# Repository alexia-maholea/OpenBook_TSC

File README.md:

# OpenBook E-Reader
Maholea Elena-Alexia, 333CD

## Viziune de ansamblu a proiectului

## Schema bloc

# Bill of Materials
|**Part Name**                                               | **Check Price** | **DataSheet** |
|-------------------------------------------------------------|------------------|---------------|
|BUTTON| [Check Price](https://industry.panasonic.com/global/en/products/control/switch/light-touch/number/evqpuj02k)     |   [DataSheet](https://industry.panasonic.com/global/en/products/control/switch/light-touch/number/evqpuj02k)      
| ESP32_WROVER_EAGLE-LTSPICE_CC0402                          | [Check Price](https://componentsearchengine.com/part-view/CC0402MRX5R5BB106/YAGEO)      | [DataSheet](https://componentsearchengine.com/part-view/CC0402MRX5R5BB106/YAGEO)   |
|CPH3225A                                                    | [Check Price](https://www.snapeda.com/parts/CPH3225A/Seiko+Instruments/view-part/?ref=eda)      | [DataSheet](https://www.snapeda.com/parts/CPH3225A/Seiko+Instruments/view-part/?ref=eda)     |
|ADAFRUIT_LEDCHIP-LED0603                                    | [Check Price](https://www.snapeda.com/parts/KP-1608SURCK/Kingbright/view-part/?ref=search&t=LED%200603)      | [DataSheet]()     |
|USBLC6-2SC6Y                                                | [Check Price](https://www.google.com/url?q=https://www.snapeda.com/parts/USBLC6-2SC6Y/STMicroelectronics/view-part/?ref%3Deda&sa=D&source=editors&ust=1743979629785640&usg=AOvVaw2X7DsyD0aSaihvCPkvpMcS)      | [DataSheet](https://www.google.com/url?q=https://www.snapeda.com/parts/USBLC6-2SC6Y/STMicroelectronics/view-part/?ref%3Deda&sa=D&source=editors&ust=1743979629785640&usg=AOvVaw2X7DsyD0aSaihvCPkvpMcS)     |
|MBR0530                                                     | [Check Price](https://www.google.com/url?q=https://eu.mouser.com/ProductDetail/KYOCERA-AVX/SD0805S020S1R0?qs%3DjCA%25252BPfw4LHbpkAoSnwrdjw%253D%253D&sa=D&source=editors&ust=1743979672575299&usg=AOvVaw260GDj91204P1ItqGdSVkk)      | [DataSheet](https://www.google.com/url?q=https://eu.mouser.com/ProductDetail/KYOCERA-AVX/SD0805S020S1R0?qs%3DjCA%25252BPfw4LHbpkAoSnwrdjw%253D%253D&sa=D&source=editors&ust=1743979672575299&usg=AOvVaw260GDj91204P1ItqGdSVkk)     |
|PGB1010603MR                                                | [Check Price](https://www.snapeda.com/parts/PGB1010603MR/Littelfuse/view-part/?ref=eda)      | [DataSheet](https://www.snapeda.com/parts/PGB1010603MR/Littelfuse/view-part/?ref=eda)     |
| ESP32_WROVER_AVX---SD0805S020S1R0_AVX_...                  | [Check Price](https://eu.mouser.com/ProductDetail/KYOCERA-AVX/SD0805S020S1R0?qs=jCA%252BPfw4LHbpkAoSnwrdjw%3D%3D)      | [DataSheet](https://eu.mouser.com/ProductDetail/KYOCERA-AVX/SD0805S020S1R0?qs=jCA%252BPfw4LHbpkAoSnwrdjw%3D%3D)     |
| PGB1010603MR                                                | [Check Price](https://www.snapeda.com/parts/PGB1010603MR/Littelfuse/view-part/?ref=eda)      | [DataSheet](https://www.snapeda.com/parts/PGB1010603MR/Littelfuse/view-part/?ref=eda)     |
|BD5229G-TR                                                  | [Check Price](https://componentsearchengine.com/part-view/BD5229G-TR/ROHM%20Semiconductor)      | [DataSheet](https://componentsearchengine.com/part-view/BD5229G-TR/ROHM%20Semiconductor)     |
|XC6220A331MR-G                                              | [Check Price](https://componentsearchengine.com/part-view/XC6220A331MR-G/Torex)      | [DataSheet](https://componentsearchengine.com/part-view/XC6220A331MR-G/Torex)     |
|FH34SRJ-24S-0.5SH_99_                                       | [Check Price](https://componentsearchengine.com/part-view/XC6220A331MR-G/Torex)      | [DataSheet](https://componentsearchengine.com/part-view/XC6220A331MR-G/Torex)     |
|SAMACSYS_PARTS_USB4110-GF-A                                | [Check Price](https://componentsearchengine.com/part-view/USB4110-GF-A/GCT%20(GLOBAL%20CONNECTOR%20TECHNOLOGY)) | [DataSheet](https://componentsearchengine.com/part-view/USB4110-GF-A/GCT%20(GLOBAL%20CONNECTOR%20TECHNOLOGY)) |
|QWIIC_CONNECTORJS-1MM                                       | #N/A             | #N/A          |
|112A-TAAR-R03_ATTEND                                        | #N/A      | #N/A     |
|744043680IND_4828-WE-TPC_WRE                                | [Check Price](https://eu.mouser.com/ProductDetail/Wurth-Elektronik/744043680?qs=PGXP4M47uW6VkZq%252BkzjrHA%3D%3D)      | [DataSheet](https://eu.mouser.com/ProductDetail/Wurth-Elektronik/744043680?qs=PGXP4M47uW6VkZq%252BkzjrHA%3D%3D)     |
| PFMF.050.1                                      | [Check Price](https://www.mouser.co.uk/ProductDetail/EPCOS-TDK/B72520T0350K062?qs=dEfas%2FXlABIszF52uu7vrg%3D%3D)      | [DataSheet](https://www.mouser.co.uk/ProductDetail/EPCOS-TDK/B72520T0350K062?qs=dEfas%2FXlABIszF52uu7vrg%3D%3D)     |
|ESP32_WROVER_SPARKFUN-DISCRETESEMI_MOSFET_...             | [Check Price](https://componentsearchengine.com/part-view/DMG2305UX-7/Diodes%20Incorporated)      | [DataSheet](https://componentsearchengine.com/part-view/DMG2305UX-7/Diodes%20Incorporated)     |
|SJ                                                          | [Check Price](https://grabcad.com/library/solder-jumpers-1)      | [DataSheet](https://grabcad.com/library/solder-jumpers-1)     |
|ESP32_WROVER_EAGLE-LTSPICE_RR0402           | [Check Price](https://componentsearchengine.com/part-view/R0402%201%25%20100%20K%20(RC0402FR-07100KL)/YAGEO)         | [DataSheet](https://componentsearchengine.com/part-view/R0402%201%25%20100%20K%20(RC0402FR-07100KL)/YAGEO)       |
|W25Q512JVEIQ                                   | [Check Price](https://www.snapeda.com/parts/W25Q512JVEIQ/Winbond+Electronics/view-part/?ref=eda)         | [DataSheet](https://www.snapeda.com/parts/W25Q512JVEIQ/Winbond+Electronics/view-part/?ref=eda)       |
|ESP32-C6-WROOM-1-N8                            | [Check Price](https://www.snapeda.com/parts/ESP32-C6-WROOM-1-N8/Espressif+Systems/view-part/?ref=eda)         | [DataSheet](https://www.snapeda.com/parts/ESP32-C6-WROOM-1-N8/Espressif+Systems/view-part/?ref=eda)       |
|DS3231SN#                                      | [Check Price](https://www.snapeda.com/parts/DS3231SN%23/Analog+Devices/view-part/?ref=eda)         | [DataSheet](https://www.snapeda.com/parts/DS3231SN%23/Analog+Devices/view-part/?ref=eda)       |
|MAX17048G+T10                                  | [Check Price](https://www.snapeda.com/parts/MAX17048G+T10/Analog+Devices/view-part/?ref=eda)         | [DataSheet](https://www.snapeda.com/parts/MAX17048G+T10/Analog+Devices/view-part/?ref=eda)       |
|ESP32_WROVER_SPARKFUN-IC-POWER_MCP73831        | #N/A         | #N/A       |

## Descriere a functionalitatii componentelor hardware

OpenBook E-Reader este un dispozitiv portabil bazat pe ESP32-C3 WROOM, dotat cu un display e-ink de 1.5” (200x200 px) și alimentat de o baterie Li-Po. Proiectul optimizează consumul energetic și permite citirea cărților stocate pe card SD.

# Componente și interfețe

## Alimentare si Baterie

Sistemul poate fi alimentat fie prin portul USB-C, fie dintr-o baterie Li-Po, oferind flexibilitate in utilizare. Tensiunea de 5V furnizata de USB este folosita in paralel de doua componente:

- Un **controller de incarcare** pentru acumulatorul Li-Po
- Un **regulator LDO** care transforma cei 5V in 3.3V

Tensiunea de 3.3V alimenteaza toate componentele esentiale: microcontrolerul ESP32-C6, senzorii si afisajul. Cand sursa USB nu este conectata, bateria preia automat alimentarea intregului sistem.

## Microcontroler

La baza functionarii sta un **ESP32-C6**, responsabil cu:

- Rularea firmware-ului principal
- Conectarea la retele wireless (Wi-Fi 6 si BLE)
- Citirea datelor de la senzorii interni
- Afisarea informatiilor pe display-ul E-Paper
- Gestionarea memoriei externe: atat Flash NOR, cat si card microSD

## Senzori si RTC

Dispozitivul integreaza doi senzori conectati prin magistrala I2C:

- **BME688** – masoara temperatura, umiditatea, presiunea si compusi volatili
- **DS3231** – ceas de timp real (RTC) cu precizie ridicata

Prin I2C, datele sunt colectate rapid si trimise catre microcontroler pentru prelucrare.

## Display E-Paper

Afisajul de tip E-Paper comunica cu microcontrolerul prin interfata SPI si include urmatorii pini de control:

- `EPD_CS` (chip select)
- `EPD_DC` (data/command)
- `EPD_RST` (reset)
- `EPD_BUSY` (semnal de ocupat)

Actualizarea continutului pe ecran se face la cerere, iar consumul de energie este practic zero atunci cand imaginea este statica.

## Extensii si Stocare

Sistemul este gandit sa suporte si senzori aditionali printr-un conector compatibil **Qwiic / Stemma QT**, care extinde magistrala I2C. De asemenea, un **slot microSD** permite utilizatorului sa adauge fisiere externe (setari, loguri, eBooks etc.), iar o **memorie Flash NOR** dedicata stocheaza resurse interne precum firmware-ul, fonturile sau alte date statice.

# Mapping pini pentru EPS32-C6

| **Pin ESP32-C6** | **Nume/Funcție**        | **Componentă / Scop**                |
|------------------|-------------------------|--------------------------------------|
| 2                | 3V3                     | Alimentare ESP32                     |
| 1                | GND                     | Împământare                          |
| 15 (GPIO0)       | IO/BOOT                 | Mod boot pentru programare           |
| 3                | RESET                   | Reset ESP32                          |
| 23 (GPIO16)      | TXD0                    | UART TX – comunicație serială        |
| 24 (GPIO17)      | RXD0                    | UART RX – comunicație serială        |
| 27               | MISO                    | SPI – date de la dispozitiv          |
| 10               | MOSI                    | SPI – date către dispozitiv          |
| 7                | SCK                     | SPI – semnal de ceas                 |
| 4                | SS/SD                   | SPI CS – SD card                     |
| 11               | EPD_CS                  | SPI CS – e-paper                     |
| 12               | FLASH_CS                | SPI CS – Flash                       |
| 26               | EPD_BUSY                | Status e-paper                       |
| 5                | EPD_DC                  | Date/Comandă e-paper                 |
| 21               | EPD_RST                 | Reset e-paper                        |
| 18               | EPD_3V3_C               | Alimentare controlată e-paper        |
| 19               | SDA                     | I2C – date                           |
| 20               | SCL                     | I2C – ceas                           |
| 17               | I2C_PW                  | Alimentare pentru I2C (opțional)     |
| 16               | RTC_RST                 | Reset RTC                            |
| 8                | INT RTC                 | Interrupt RTC                        |
| 9                | 32KHZ                   | Oscilator extern RTC                 |
| 13, 14           | USB D-, USB D+          | Comunicare USB                       |
| 25               | IO/CHANGE               | Pin general sau întrerupere          |

# Procesul de realizare al proiectului

- In realizarea schematicului, am urmarit exact fisierul de pe OCW, iar
pentru PCB, am respectat dimensiunile si am incercat sa plasez componentele dinauntru
cat mai lizibil.

- Am realizat planurile de masa cu semnalul GND atatp e top, cat si pe bottom. Am
aplicat via stitching si am amplasat vias-urile langa antena.

- M-am folosit de autorouting pentru traseele de rutare. Am respectat cerintele de pe ocw, in legatura cu dimensiunea firelor de cupru, respectiv minim 0.30mm pentru traseele de putere si 0.15 pentru restul.

- TP-urile au fost amplasate dupa cum am considerat ca ar fi mai eficient pentru rutare
pentru a fi aproape de componentele la care sunt conectate

- Dupa ce am trecut in 3D, am adaugat componentele si le-am creat/editat modelele 3D cat sa fie asezate corespunzator pe placa.

- Pentru a scapa de erorile aparute, am efectuat diferite actiuni:
    - Pentru erorile de tip SMD-Hole, am dat Approve dupa cum ni s-a specificat
    - Pentru alte tipuri de erori, a fost nevoie sa modific footprint-ul componentelor sau sa mut firele de pe placa

- Am realizat si modele 3D pentru baterie si display, conform documentelor oferite. Am
incercat pe cat mai mult sa respect dimensiunile pentru a nu avea probleme la amplasare.

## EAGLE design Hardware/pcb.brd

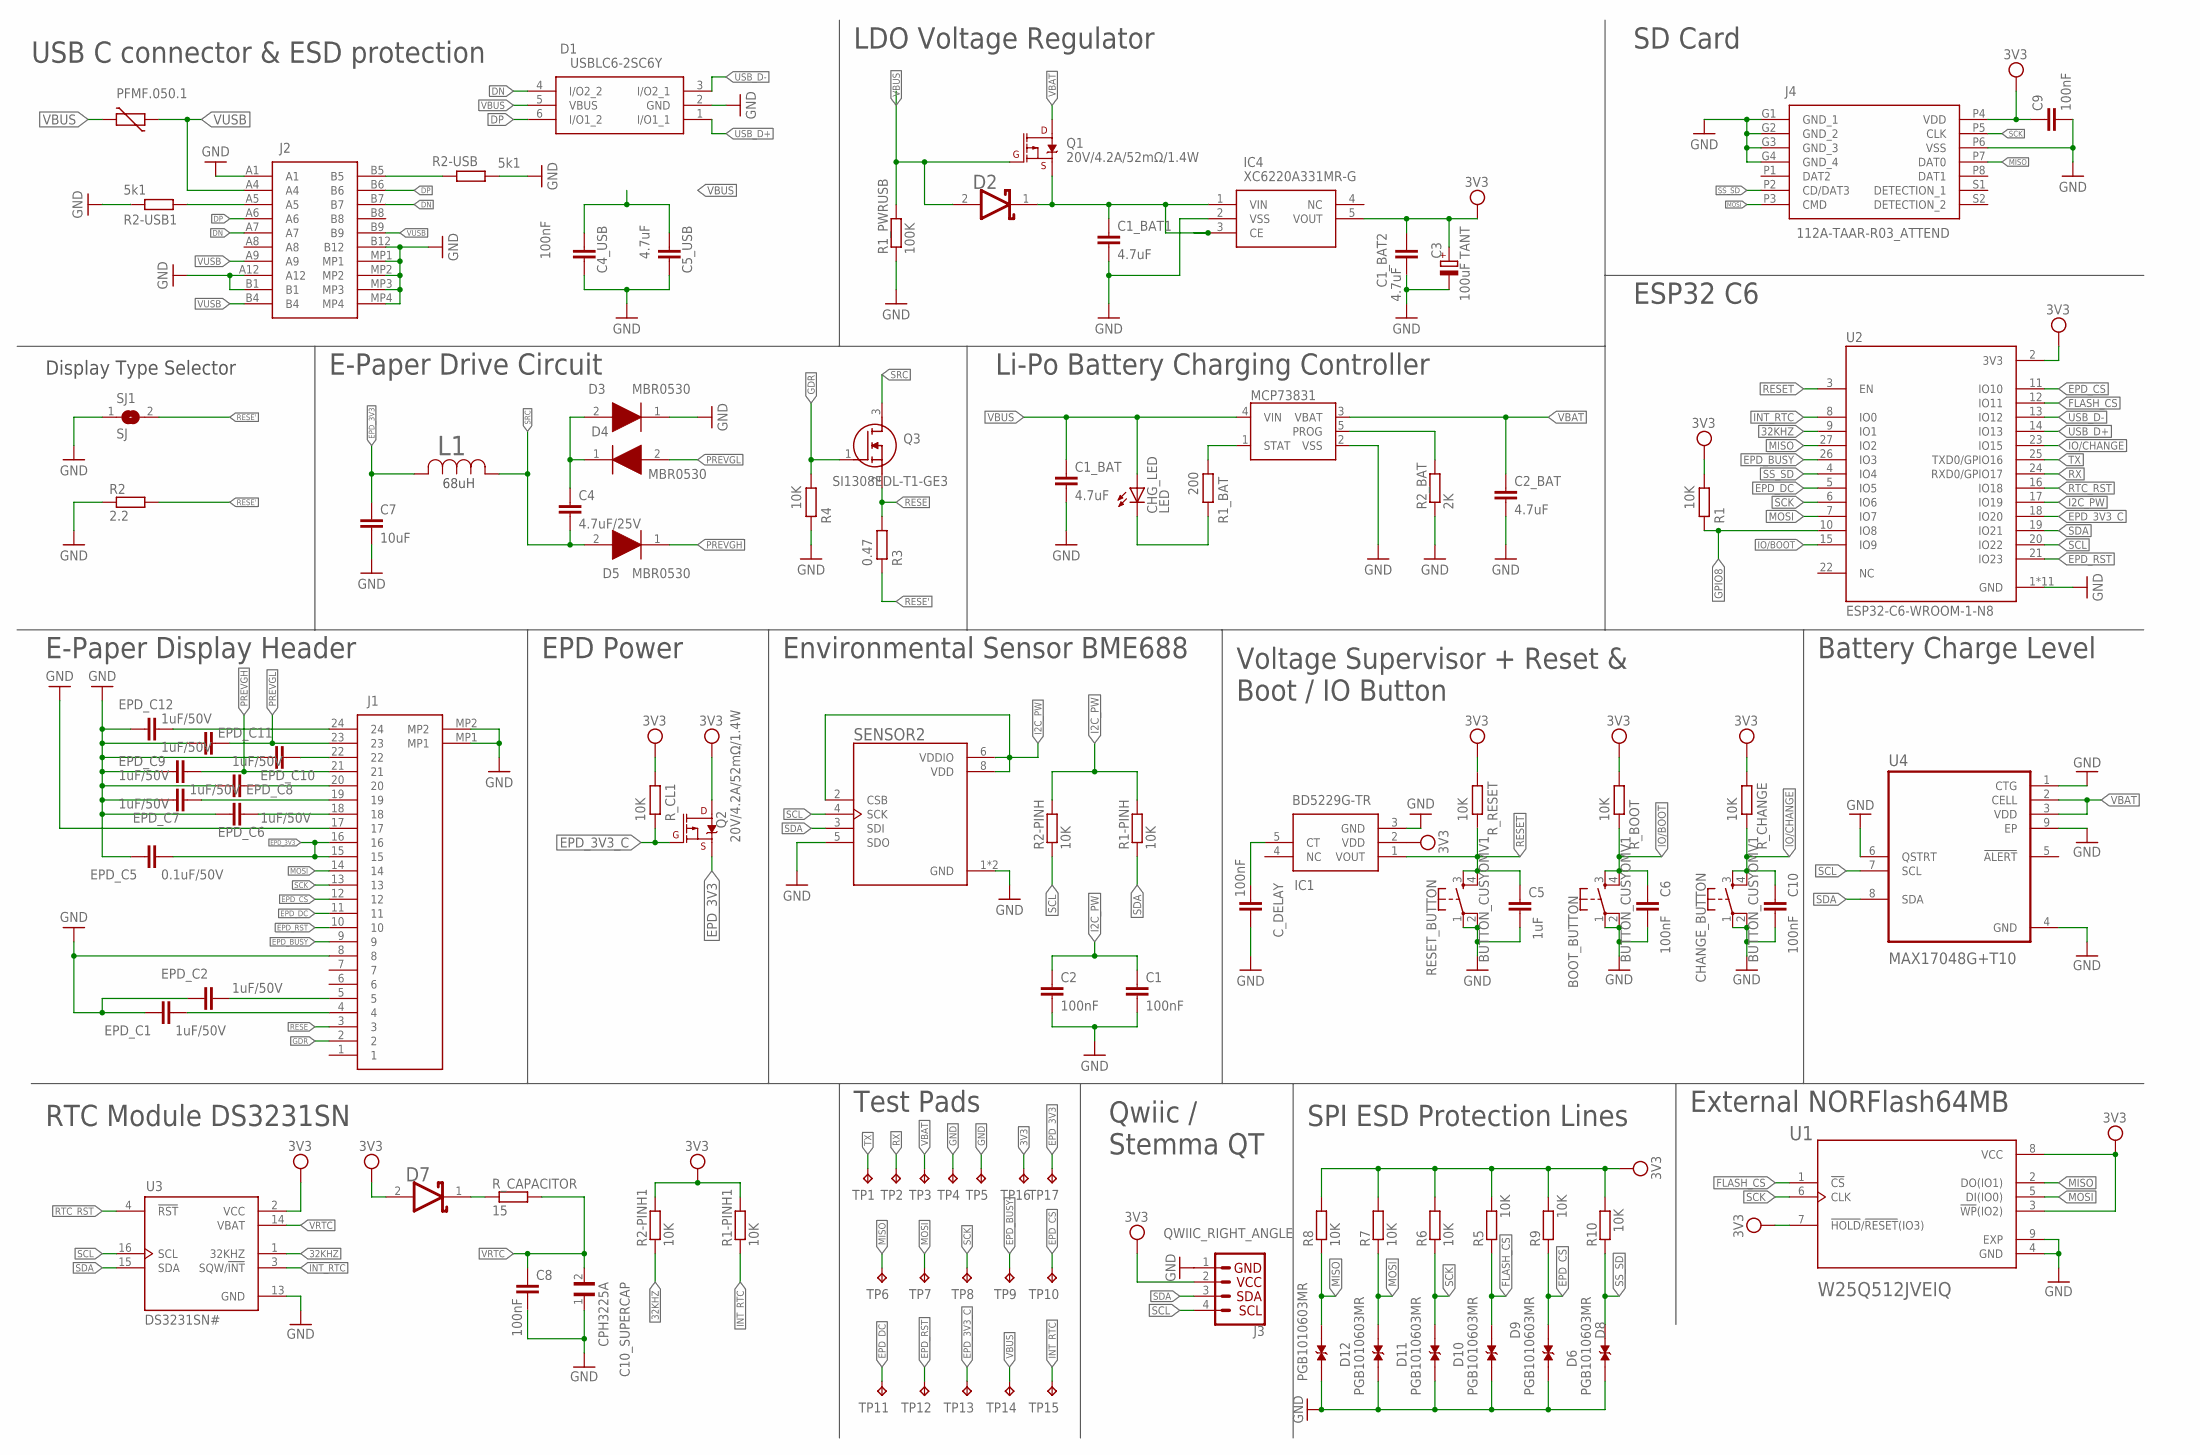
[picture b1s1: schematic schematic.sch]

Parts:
BOOT_BUTTON: BUTTON_CUSYOMV1; MYBUTTON
C1, C2, C4_USB, C6, C8, C9, C10: 100nF; EAGLE-LTSPICE_C0402
C1_BAT, C1_BAT1, C1_BAT2, C2_BAT, C5_USB: 4.7uF; EAGLE-LTSPICE_C0402
C3: 100uF TANT; RCL_CT3528
C4: 4.7uF/25V; EAGLE-LTSPICE_C0402
C5: 1uF; EAGLE-LTSPICE_C0402
C7: 10uF; EAGLE-LTSPICE_C0402
C10_SUPERCAP: CPH3225A; CAPCP3225X100N
CHANGE_BUTTON: BUTTON_CUSYOMV1; MYBUTTON
CHG_LED: LED; ADAFRUIT_CHIP-LED0603
C_DELAY: 100nF; EAGLE-LTSPICE_C0402
D1: USBLC6-2SC6Y; SOT95P280X145-6N
D2, D7: ESP32_WROVER_AVX---SD0805S020S1R0_AVX_SD0805S020S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; ESP32_WROVER_AVX---SD0805S020S1R0_AVX_SD0805S020S1R0_0
D3, D4, D5: MBR0530; SOD3716X135N
D6, D8, D9, D10, D11, D12: PGB1010603MR; DIOC1608X36N
EPD_C1, EPD_C2, EPD_C6, EPD_C7, EPD_C8, EPD_C9, EPD_C10, EPD_C11, EPD_C12: 1uF/50V; EAGLE-LTSPICE_C0402
EPD_C5: 0.1uF/50V; EAGLE-LTSPICE_C0402
IC1: BD5229G-TR; SOT95P280X125-5N
IC4: XC6220A331MR-G; SOT95P280X120-5N
J1: FH34SRJ-24S-0.5SH_99_; FH34SRJ24S05SH99
J2: SAMACSYS_PARTS_USB4110-GF-A; SAMACSYS_PARTS_USB4110GFA
J3: QWIIC_RIGHT_ANGLE; JST04_1MM_RA
J4: 112A-TAAR-R03_ATTEND; 112ATAARR03ATTEND
L1: 68uH; IND_4828-WE-TPC_WRE
MCP73831: ESP32_WROVER_SPARKFUN-IC-POWER_MCP73831; ESP32_WROVER_SPARKFUN-IC-POWER_SOT23-5
PFMF.050.1: ESP32C6_VARISTORCN1812; ESP32C6_VARISTOR_CT/CN1812
Q1, Q2: 20V/4.2A/52mΩ/1.4W; ESP32_WROVER_SPARKFUN-DISCRETESEMI_SOT23-3
Q3: SI1308EDL-T1-GE3; SOT65P210X110-3N
R1, R1-PINH, R1-PINH1, R2-PINH, R2-PINH1, R4, R5, R6, R7, R8, R9, R10: 10K; ESP32_WROVER_EAGLE-LTSPICE_R0402
R1_BAT: 200; ESP32_WROVER_EAGLE-LTSPICE_R0402
R1_PWRUSB: 100K; ESP32_WROVER_EAGLE-LTSPICE_R0402
R2: 2.2; ESP32_WROVER_EAGLE-LTSPICE_R0402
R2-USB, R2-USB1: 5k1; ESP32_WROVER_EAGLE-LTSPICE_R0402
R2_BAT: 2K; ESP32_WROVER_EAGLE-LTSPICE_R0402
R3: 0.47; ESP32_WROVER_EAGLE-LTSPICE_R0402
RESET_BUTTON: BUTTON_CUSYOMV1; MYBUTTON
R_BOOT: 10K; ESP32_WROVER_EAGLE-LTSPICE_R0402
R_CAPACITOR: 15; ESP32_WROVER_EAGLE-LTSPICE_R0402
R_CHANGE: 10K; ESP32_WROVER_EAGLE-LTSPICE_R0402
R_CL1: 10K; ESP32_WROVER_EAGLE-LTSPICE_R0402
R_RESET: 10K; ESP32_WROVER_EAGLE-LTSPICE_R0402
SENSOR2: ESP32_WROVER_BME680_BME680; ESP32_WROVER_BME680_PSON80P300X300X100-8N
SJ1: SJ
TP1, TP2, TP3, TP4, TP5, TP6, TP7, TP8, TP9, TP10, TP11, TP12, TP13, TP14, TP15, TP16, TP17: TPTP20R; TP20R
U1: W25Q512JVEIQ; SON127P600X800X80-9N
U2: ESP32-C6-WROOM-1-N8; XCVR_ESP32-C6-WROOM-1-N8
U3: DS3231SN#; SOIC127P1032X265-16N
U4: MAX17048G+T10; SON50P200X200X80-9N

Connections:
3V3: C1_BAT2.1, C3.+, C9.1, D7.2 (ANODE), IC1.2 (VDD), IC4.5 (VOUT), J3.2, J4.P4 (VDD), Q2.3 (D), R1.2, R1-PINH1.2, R2-PINH1.2, R5.2, R6.2, R7.2, R8.2, R9.2, R10.2, R_BOOT.2, R_CHANGE.2, R_CL1.2, R_RESET.2, TP16.TP, U1.3 (!WP!(IO2)), U1.7 (!HOLD!/!RESET!(IO3)), U1.8 (VCC), U2.2 (3V3), U3.2 (VCC)
32KHZ: R2-PINH1.1, U2.9 (IO1), U3.1 (32KHZ)
DN: D1.4 (I/O2_2), J2.A7, J2.B7
DP: D1.6 (I/O1_2), J2.A6, J2.B6
EPD_3V3: C7.1, EPD_C5.1, J1.15, J1.16, L1.2, Q2.2 (S), TP17.TP
EPD_3V3_C: Q2.1 (G), R_CL1.1, TP13.TP, U2.18 (IO20)
EPD_BUSY: J1.9, TP9.TP, U2.26 (IO3)
EPD_CS: D6.2, J1.12, R9.1, TP10.TP, U2.11 (IO10)
EPD_DC: J1.11, TP11.TP, U2.5 (IO5)
EPD_RST: J1.10, TP12.TP, U2.21 (IO23)
FLASH_CS: D9.2, R5.1, U1.1 (!CS), U2.12 (IO11)
GDR: J1.2, Q3.1 (G), R4.2
GND: BOOT_BUTTON.1, BOOT_BUTTON.2, C1.2, C1_BAT.2, C1_BAT1.2, C1_BAT2.2, C2.2, C2_BAT.2, C3.-, C4_USB.2, C5.2, C5_USB.2, C6.2, C7.2, C8.2, C9.2, C10.2, C10_SUPERCAP.1, CHANGE_BUTTON.1, CHANGE_BUTTON.2, C_DELAY.2, D1.2 (GND), D3.1 (K), D6.1, D8.1, D9.1, D10.1, D11.1, D12.1, EPD_C1.2, EPD_C2.2, EPD_C5.2, EPD_C6.2, EPD_C7.2, EPD_C8.2, EPD_C9.2, EPD_C10.2, EPD_C11.2, EPD_C12.2, IC1.3 (GND), IC4.2 (VSS), J1.8, J1.17, J1.MP1, J1.MP2, J2.A1, J2.A12, J2.B1, J2.B12, J2.MP1, J2.MP2, J2.MP3, J2.MP4, J3.1, J4.G1 (GND_1), J4.G2 (GND_2), J4.G3 (GND_3), J4.G4 (GND_4), J4.P6 (VSS), MCP73831.2 (VSS), R1_PWRUSB.1, R2.1, R2-USB.1, R2-USB1.1, R2_BAT.1, R4.1, RESET_BUTTON.1, RESET_BUTTON.2, SENSOR2.1 (GND), SENSOR2.5 (SDO), SENSOR2.7 (GND), SJ1.1, TP4.TP, TP5.TP, U1.4 (GND), U1.9 (EXP), U2.1 (GND), U2.28 (GND), U2.29_1 (GND), U2.29_2 (GND), U2.29_3 (GND), U2.29_4 (GND), U2.29_5 (GND), U2.29_6 (GND), U2.29_7 (GND), U2.29_8 (GND), U2.29_9 (GND), U3.13 (GND), U4.1 (CTG), U4.4 (GND), U4.6 (QSTRT), U4.9 (EP)
GPIO8: R1.1, U2.10 (IO8)
I2C_PW: C1.1, C2.1, R1-PINH.2, R2-PINH.2, SENSOR2.2 (CSB), SENSOR2.6 (VDDIO), SENSOR2.8 (VDD), U2.17 (IO19)
INT_RTC: R1-PINH1.1, TP15.TP, U2.8 (IO0), U3.3 (SQW/!INT)
IO/BOOT: BOOT_BUTTON.3, BOOT_BUTTON.4, C6.1, R_BOOT.1, U2.15 (IO9)
IO/CHANGE: C10.1, CHANGE_BUTTON.3, CHANGE_BUTTON.4, R_CHANGE.1, U2.23 (IO15)
MISO: D12.2, J4.P7 (DAT0), R8.1, TP6.TP, U1.2 (DO(IO1)), U2.27 (IO2)
MOSI: D11.2, J1.14, J4.P3 (CMD), R7.1, TP7.TP, U1.5 (DI(IO0)), U2.7 (IO7)
unnamed: J2.A5, R2-USB1.2
unnamed: J2.B5, R2-USB.2
unnamed: C1_BAT1.1, D2.1 (CATHODE), IC4.1 (VIN), IC4.3 (CE), Q1.2 (S)
unnamed: C4.1, D3.2 (A), D4.1 (K)
unnamed: MCP73831.1 (STAT), R1_BAT.2
unnamed: CHG_LED.C, R1_BAT.1
unnamed: MCP73831.5 (PROG), R2_BAT.2
unnamed: EPD_C12.1, J1.24
unnamed: C_DELAY.1, IC1.5 (CT)
unnamed: EPD_C10.1, J1.22
unnamed: EPD_C8.1, J1.20
unnamed: EPD_C7.1, J1.19
unnamed: EPD_C6.1, J1.18
unnamed: EPD_C1.1, J1.4
unnamed: EPD_C2.1, J1.5
unnamed: D7.1 (CATHODE), R_CAPACITOR.1
PREVGH: D5.1 (K), EPD_C9.1, J1.21
PREVGL: D4.2 (A), EPD_C11.1, J1.23
RESE: J1.3, Q3.2 (S), R3.2
RESE': R2.2, R3.1, SJ1.2
RESET: C5.1, IC1.1 (VOUT), RESET_BUTTON.3, RESET_BUTTON.4, R_RESET.1, U2.3 (EN)
RTC_RST: U2.16 (IO18), U3.4 (!RST)
RX: TP2.TP, U2.24 (RXD0/GPIO17)
SCK: D10.2, J1.13, J4.P5 (CLK), R6.1, TP8.TP, U1.6 (CLK), U2.6 (IO6)
SCL: J3.4, R2-PINH.1, SENSOR2.4 (SCK), U2.20 (IO22), U3.16 (SCL), U4.7 (SCL)
SDA: J3.3, R1-PINH.1, SENSOR2.3 (SDI), U2.19 (IO21), U3.15 (SDA), U4.8 (SDA)
SRC: C4.2, D5.2 (A), L1.1, Q3.3 (D)
SS_SD: D8.2, J4.P2 (CD/DAT3), R10.1, U2.4 (IO4)
TX: TP1.TP, U2.25 (TXD0/GPIO16)
USB_D+: D1.1 (I/O1_1), U2.14 (IO13)
USB_D-: D1.3 (I/O2_1), U2.13 (IO12)
VBAT: C2_BAT.1, MCP73831.3 (VBAT), Q1.3 (D), TP3.TP, U4.2 (CELL), U4.3 (VDD)
VBUS: C1_BAT.1, C4_USB.1, C5_USB.1, CHG_LED.A, D1.5 (VBUS), D2.2 (ANODE), MCP73831.4 (VIN), PFMF.050.1.2, Q1.1 (G), R1_PWRUSB.2, TP14.TP
VRTC: C8.1, C10_SUPERCAP.2, R_CAPACITOR.2, U3.14 (VBAT)
VUSB: J2.A4, J2.A9, J2.B4, J2.B9, PFMF.050.1.1

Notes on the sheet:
USB C connector & ESD protection
LDO Voltage Regulator
SD Card
Display Type Selector
E-Paper Drive Circuit
Li-Po Battery Charging Controller
ESP32 C6
Battery Charge Level
Voltage Supervisor + Reset & Boot / IO Button
Environmental Sensor BME688
EPD Power
E-Paper Display Header
RTC Module DS3231SN
Test Pads
Qwiic / Stemma QT
External NORFlash64MB
SPI ESD Protection Lines
68uH

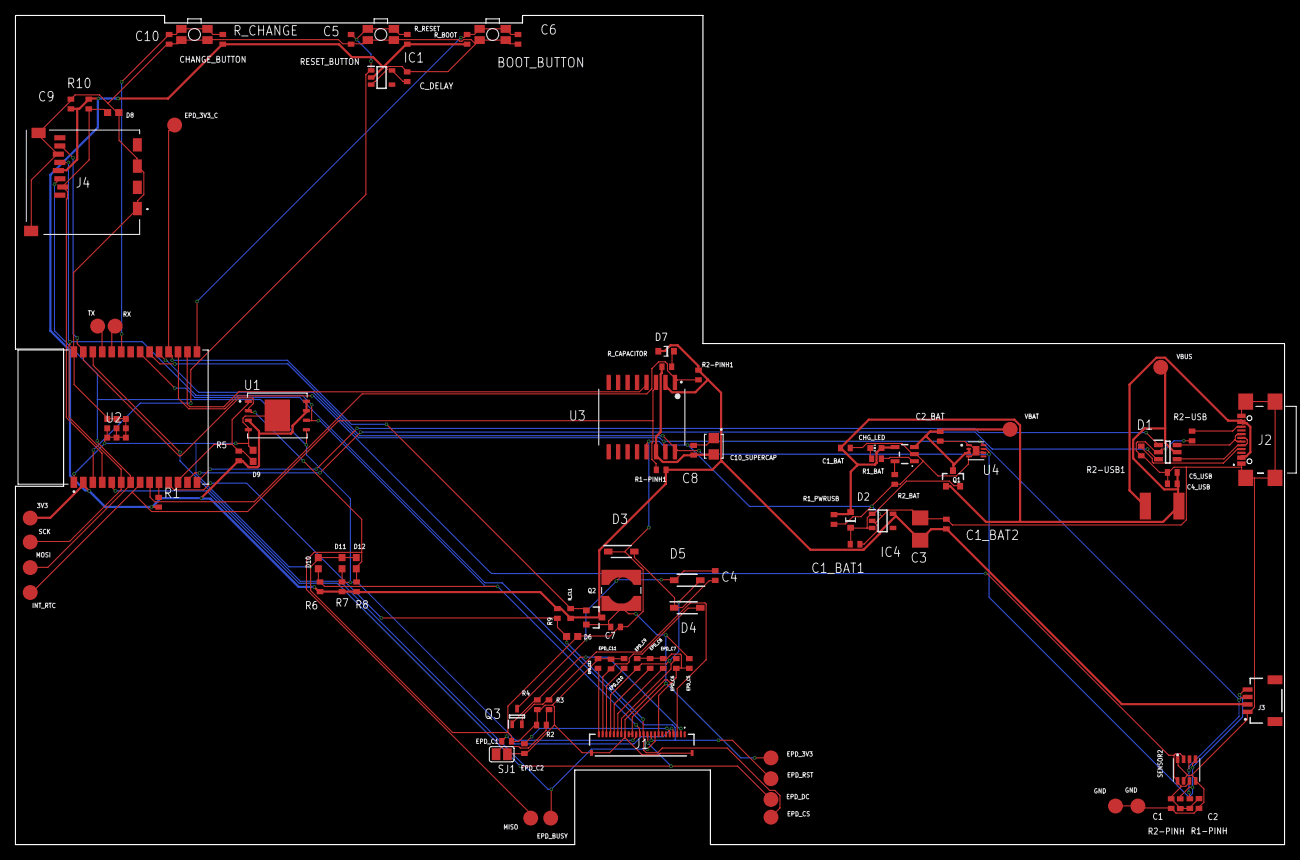
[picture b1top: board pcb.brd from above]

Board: 2 copper layers, 170.2 x 111.2 mm, 103 parts (0 on the bottom side), 55 nets.

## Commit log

2025-04-06 project 2
2025-04-06 modified
2025-04-06 typo
2025-04-13 issues fixed
2025-04-13 last issues
2025-04-13 Readme

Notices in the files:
parts and their libraries:
COPYRIGHT: Copyright (C) 2024 Ultra Librarian. All rights reserved.
